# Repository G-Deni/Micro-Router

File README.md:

# Micro-Router
This project sets out to solve a simple but niche problem, when using any form of hot-spot in a large area coverage can suffer. Using a mesh-network of Micro-Routers coverage area can be extended for a short time without running any cables. This is achieved by a custom OpenWRT configuration and a onboard battery that should yield ~16hrs of run time.

## Features 

### SOM
Each Micro-Router uses a [Carambola2](https://www.8devices.com/products/carambola-2) SOM running [OpenWRT](https://openwrt.org/). 

### Ports
<ul>
  <li>USB-A - Media share capacity</li>
  <li>USB-C - Charging and UART</li>
  <li>2x RJ45 - LAN and WAN</li>
</ul>

### Charge Controller
Powered A 3.3v TP4056 charging circuit with a separate 5v boost converter to power the USB-A port. The charge controller was selected for this project to be cheap, this means while the battery is protected there is no communication between the SOM and the charge controller. There is no safe start of shut down if the battery dies the charge controller will disconnect the battery from the loads. It power switch toggles the boost converters on and off, disconnecting the battery from all loads at the boost converter. The 5v and the 3.3v boost converters are both 500mah and toggled on and off by the same slide switch.

### USB Serial
It has serial output over USB-C to help prevent bricking during development. All of the reset and clock pins are connected to make it as robust as possible, however if there is a problem with the serial connection both the Carambola2 and the serial to USB IC have reset push-buttons. 

### GPIO/SPI Headers
Exposed on the board are two 2.25mm pitch headers one is for SPI screen output (four pin) and one for general GPIO (6 pin).  

### External Antenna
A board mounted SMA connector is impedance matched for 2.4ghz WiFi is exposed for a external antenna to be connected to. There is no internal antenna as the performance is usually very poor.

### Speaker
Two pins are exposed for the speaker one is ground the other is a GPIO. One of the GPIO pins has to be reserved to be used as a speaker. If the extra GPIO pin is needed do not populate the speaker.

## Docking Case
The PCB layout may look rather unconventional but it is intentional. The routers are optimized to be used in a dock configuration.

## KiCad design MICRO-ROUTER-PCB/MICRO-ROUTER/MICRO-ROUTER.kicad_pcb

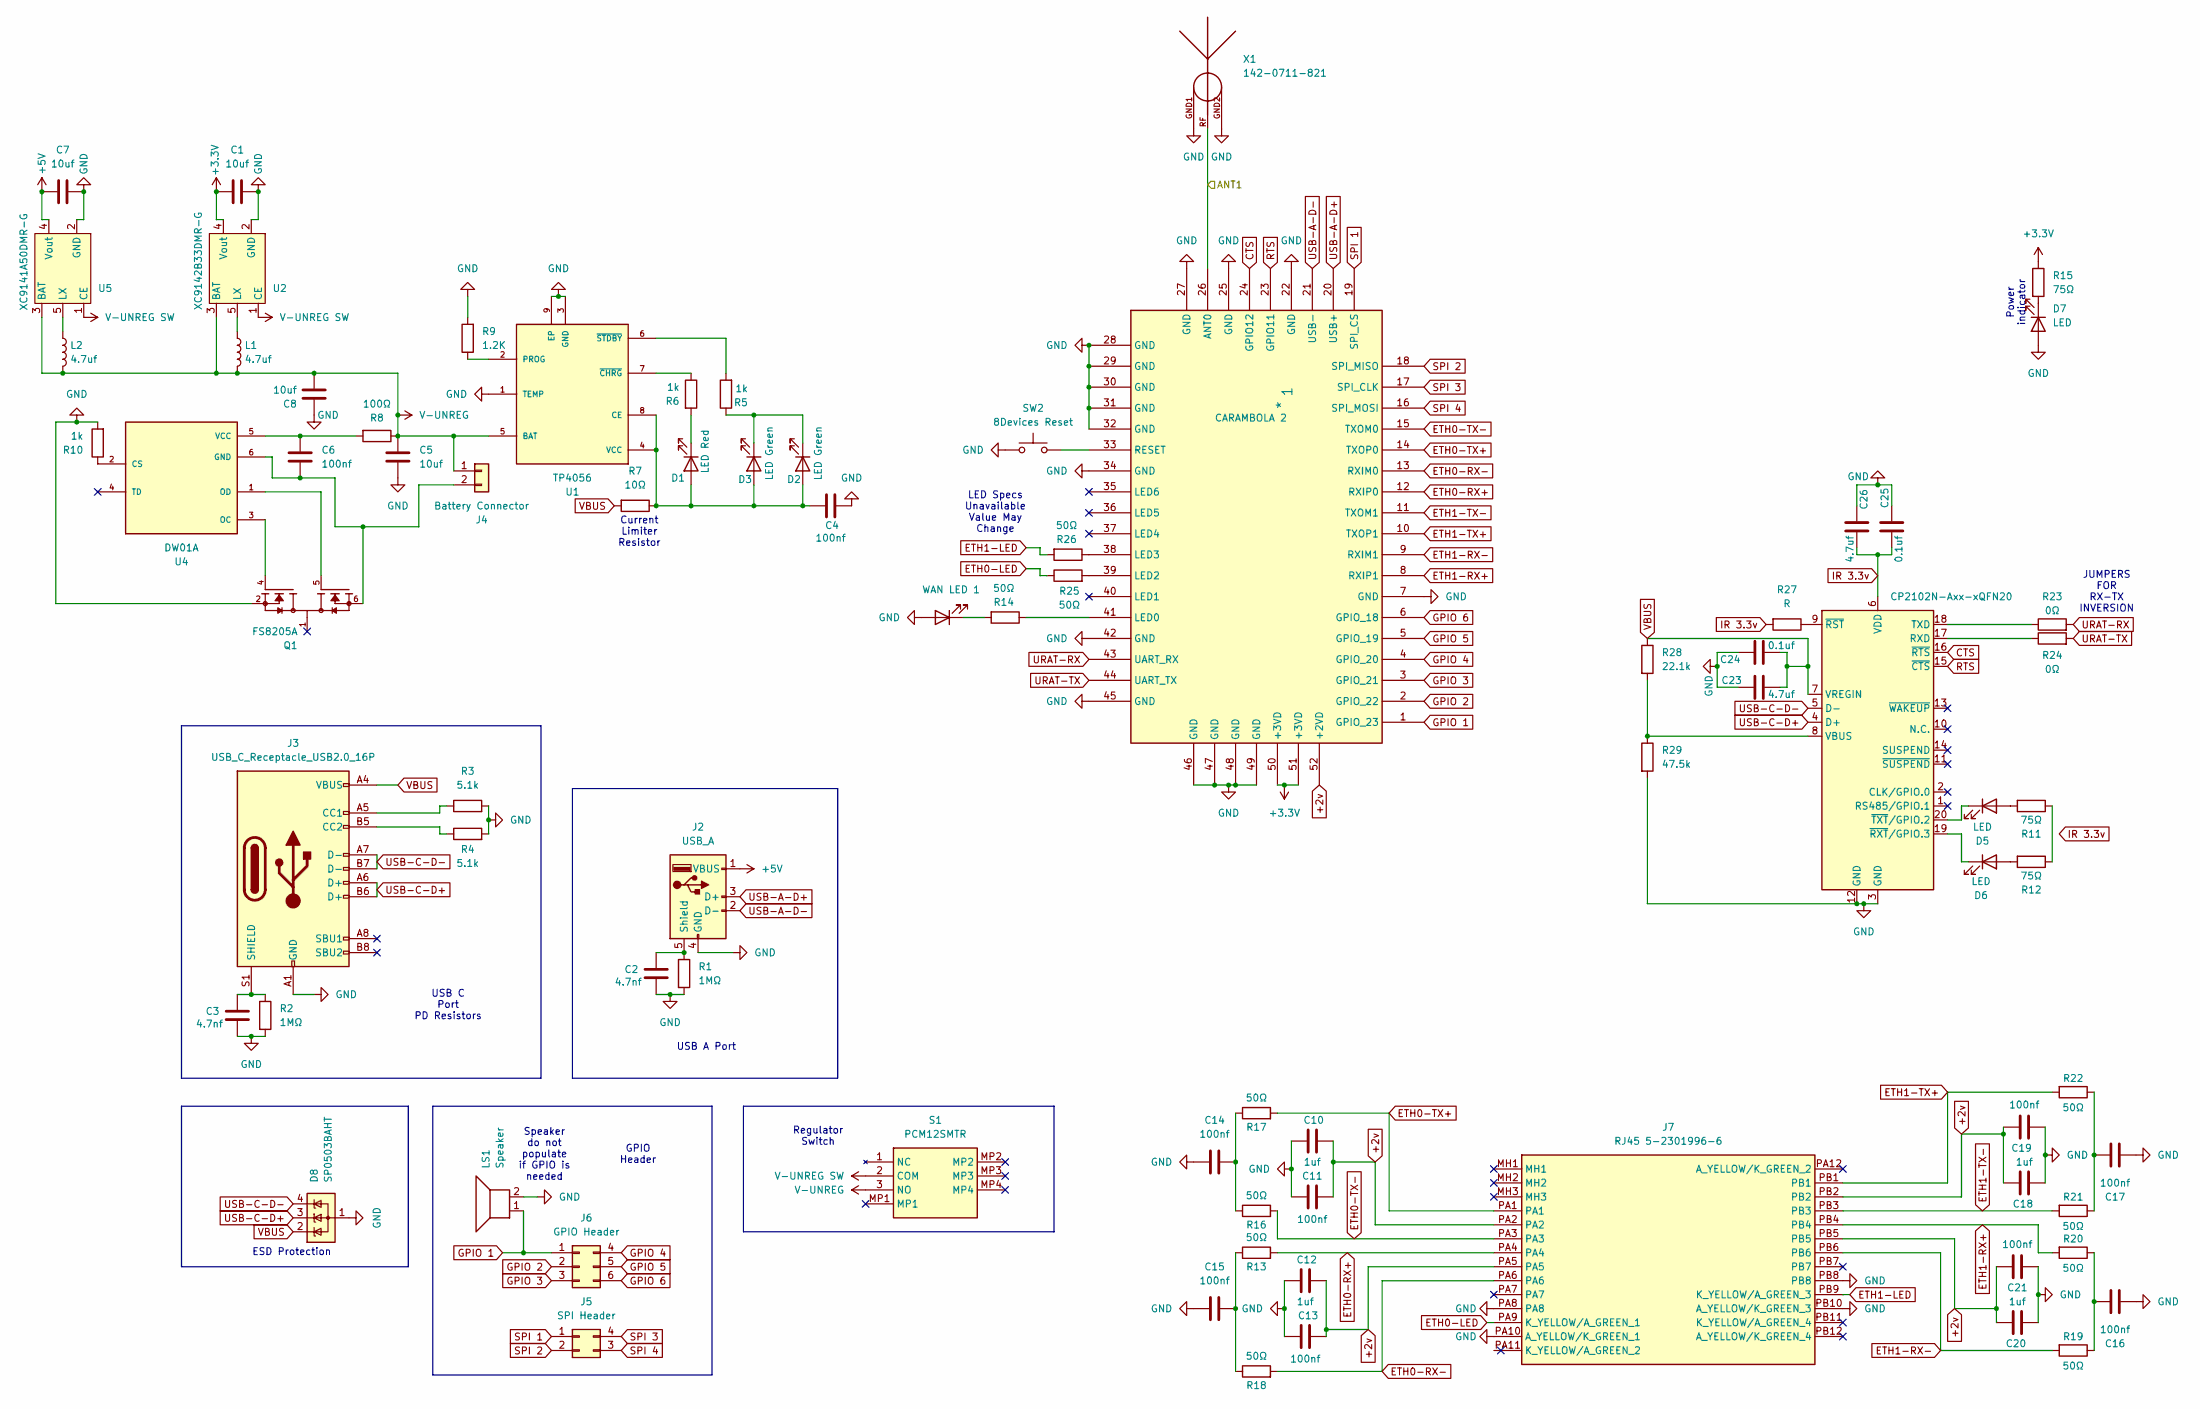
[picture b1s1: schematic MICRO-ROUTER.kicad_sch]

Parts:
1: *; 8Devices-Carambola2
C1, C5, C7, C8: 10uf; C_0603_1608Metric
C2, C3: 4.7nf; C_0603_1608Metric
C4, C6, C11, C13, C14, C15, C16, C17, C19, C21: 100nf; C_0603_1608Metric
C10, C12, C18, C20: 1uf; C_0603_1608Metric
C23, C26: 4.7uf
C24, C25: 0.1uf
D1: LED Red; LED_0603_1608Metric
D2, D3: LED Green; LED_0603_1608Metric
D4: WAN LED 1; LED_0603_1608Metric
D5, D6, D7: LED; LED_0603_1608Metric
D8: SP0503BAHT; SOT-143
J2: USB_A; USB_A_Molex_67643_Horizontal
J3: USB_C_Receptacle_USB2.0_16P; TYPE-C-31-M-12
J4: Battery Connector; PinSocket_1x02_P2.54mm_Vertical
J5: SPI Header; PinSocket_2x02_P2.54mm_Vertical
J6: GPIO Header; PinSocket_2x03_P2.54mm_Vertical
J7: RJ45 5-2301996-6; RJ45 523019966; Manufacturer_Part_Number 5-2301996-6; Mouser Part Number 571-5-2301996-6
L1, L2: 4.7uf; INDPM5752X300N
LS1: Speaker; PinSocket_1x02_P1.00mm_Vertical
Q1: FS8205A; PARTREV 1.7
R1, R2: 1MΩ; R_0603_1608Metric
R3, R4: 5.1k; R_0603_1608Metric
R5, R6, R10: 1k; R_0603_1608Metric
R7: 10Ω; R_0603_1608Metric
R8: 100Ω; R_0603_1608Metric
R9: 1.2K; R_0603_1608Metric
R11, R12, R15: 75Ω; R_0603_1608Metric
R13, R14, R16, R17, R18, R19, R20, R21, R22, R25, R26: 50Ω; R_0603_1608Metric
R23, R24: 0Ω; R_0603_1608Metric
R27: R
R28: 22.1k
R29: 47.5k
S1: PCM12SMTR; Manufacturer_Part_Number PCM12SMTR; Mouser Part Number 611-PCM12SMTR
SW2: 8Devices Reset; SW_PUSH_6mm
U1: TP4056
U2: XC9142B33DMR-G; XC8107AC20MR-G
U3: CP2102N-Axx-xQFN20; SiliconLabs_QFN-20-1EP_3x3mm_P0.5mm_EP1.8x1.8mm
U4: DW01A; PARTREV 1.8
U5: XC9141A50DMR-G; XC8107AC20MR-G
X1: 142-0711-821; SMA 142-0711-821

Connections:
+2v: 1.52 (+2VD), C10.2, C11.2, C12.2, C13.2, C18.2, C19.2, C20.2, C21.2, J7.PA2, J7.PA5, J7.PB2, J7.PB5
+3.3V: 1.50 (+3VD), 1.51 (+3VD), C1.1, R15.1, U2.4 (Vout)
+5V: C7.1, J2.1 (VBUS), U5.4 (Vout)
/ANT1: 1.26 (ANT0), X1.RF
CTS: 1.24 (GPIO12), U3.16 (~RTS)
ETH0-LED: J7.PA9 (K_YELLOW/A_GREEN_1), R25.1
ETH0-RX+: 1.12 (RXIP0), J7.PA4, R13.2
ETH0-RX-: 1.13 (RXIM0), J7.PA6, R18.2
ETH0-TX+: 1.14 (TXOP0), J7.PA1, R17.2
ETH0-TX-: 1.15 (TXOM0), J7.PA3, R16.2
ETH1-LED: J7.PB9 (K_YELLOW/A_GREEN_3), R26.2
ETH1-RX+: 1.8 (RXIP1), J7.PB4, R20.2
ETH1-RX-: 1.9 (RXIM1), J7.PB6, R19.2
ETH1-TX+: 1.10 (TXOP1), J7.PB1, R22.2
ETH1-TX-: 1.11 (TXOM1), J7.PB3, R21.2
GND: 1.7 (GND), 1.22 (GND), 1.25 (GND), 1.27 (GND), 1.28 (GND), 1.29 (GND), 1.30 (GND), 1.31 (GND), 1.32 (GND), 1.34 (GND), 1.42 (GND), 1.45 (GND), 1.46 (GND), 1.47 (GND), 1.48 (GND), 1.49 (GND), C1.2, C2.2, C3.2, C4.1, C5.1, C7.2, C8.2, C10.1, C11.1, C12.1, C13.1, C14.1, C15.1, C16.1, C17.1, C18.1, C19.1, C20.1, C21.1, C23.2, C24.2, C25.2, C26.2, D4.2 (A), D7.2 (A), D8.1 (A), J2.4 (GND), J3.A1 (GND), J3.A12 (GND), J3.B1 (GND), J3.B12 (GND), J7.PA8, J7.PA10 (A_YELLOW/K_GREEN_1), J7.PB8, J7.PB10 (A_YELLOW/K_GREEN_3), LS1.2, Q1.2, Q1.3, R1.2, R2.2, R3.2, R4.2, R9.2, R10.2, R29.2, SW2.1, U1.1 (TEMP), U1.3 (GND), U1.9 (EP), U2.2 (GND), U3.3 (GND), U3.12 (GND), U3.21 (GND), U5.2 (GND), X1.GND1, X1.GND2
GPIO 1: 1.1 (GPIO_23), J6.1, LS1.1
GPIO 2: 1.2 (GPIO_22), J6.2
GPIO 3: 1.3 (GPIO_21), J6.3
GPIO 4: 1.4 (GPIO_20), J6.4
GPIO 5: 1.5 (GPIO_19), J6.5
GPIO 6: 1.6 (GPIO_18), J6.6
unnamed: 1.41 (LED0), R14.1
unnamed: 1.39 (LED2), R25.2
unnamed: 1.38 (LED3), R26.1
unnamed: 1.33 (RESET), SW2.2
unnamed: C14.2, R16.1, R17.1
unnamed: C15.2, R13.1, R18.1
unnamed: C16.2, R19.1, R20.1
unnamed: C17.2, R21.1, R22.1
unnamed: C4.2, D1.2 (A), D2.2 (A), D3.2 (A), R7.1, U1.4 (VCC), U1.8 (CE)
unnamed: D1.1 (K), R6.2
unnamed: D2.1 (K), D3.1 (K), R5.1
unnamed: D4.1 (K), R14.2
unnamed: D5.2 (A), R11.2
unnamed: D5.1 (K), U3.20 (~TXT/GPIO.2)
unnamed: D6.2 (A), R12.2
unnamed: D6.1 (K), U3.19 (~RXT/GPIO.3)
unnamed: D7.1 (K), R15.2
unnamed: C2.1, J2.5 (Shield), R1.1
unnamed: J3.A5 (CC1), R3.1
unnamed: J3.B5 (CC2), R4.1
unnamed: C3.1, J3.S1 (SHIELD), R2.1
unnamed: C6.1, J4.2, Q1.6, Q1.7, U4.6 (GND)
unnamed: R9.1, U1.2 (PROG)
unnamed: R6.1, U1.7 (~CHRG)
unnamed: R5.2, U1.6 (~STDBY)
unnamed: L1.1, U2.5 (LX)
unnamed: R24.1, U3.17 (RXD)
unnamed: R23.1, U3.18 (TXD)
unnamed: R28.2, R29.1, U3.8 (VBUS)
unnamed: R27.1, U3.9 (~RST)
unnamed: R10.1, U4.2 (CS)
unnamed: Q1.4, U4.3 (OC)
unnamed: Q1.5, U4.1 (OD)
unnamed: C6.2, R8.2, U4.5 (VCC)
unnamed: L2.1, U5.5 (LX)
RTS: 1.23 (GPIO11), U3.15 (~CTS)
SPI 1: 1.19 (SPI_CS), J5.1
SPI 2: 1.18 (SPI_MISO), J5.2
SPI 3: 1.17 (SPI_CLK), J5.4
SPI 4: 1.16 (SPI_MOSI), J5.3
URAT-RX: 1.43 (UART_RX), R23.2
URAT-TX: 1.44 (UART_TX), R24.2
USB-A-D+: 1.20 (USB+), J2.3 (D+)
USB-A-D-: 1.21 (USB-), J2.2 (D-)
USB-C-D+: D8.3 (K), J3.A6 (D+), J3.B6 (D+), U3.4 (D+)
USB-C-D-: D8.4 (K), J3.A7 (D-), J3.B7 (D-), U3.5 (D-)
V-UNREG: C5.2, C8.1, J4.1, L1.2, L2.2, R8.1, S1.3 (NO), U1.5 (BAT), U2.3 (BAT), U5.3 (BAT)
V-UNREG SW: S1.2 (COM), U2.1 (CE), U5.1 (CE)
VBUS: C23.1, C24.1, D8.2 (K), J3.A4 (VBUS), J3.A9 (VBUS), J3.B4 (VBUS), J3.B9 (VBUS), R7.2, R28.1, U3.7 (VREGIN)

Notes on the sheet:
JUMPERS FOR RX-TX INVERSION
ESD Protection
Current Limiter Resistor
USB A Port
Power indicator
Speaker do not populate if GPIO is needed
Regulator Switch
USB C Port PD Resistors
GPIO Header
LED Specs Unavailable Value May Change

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
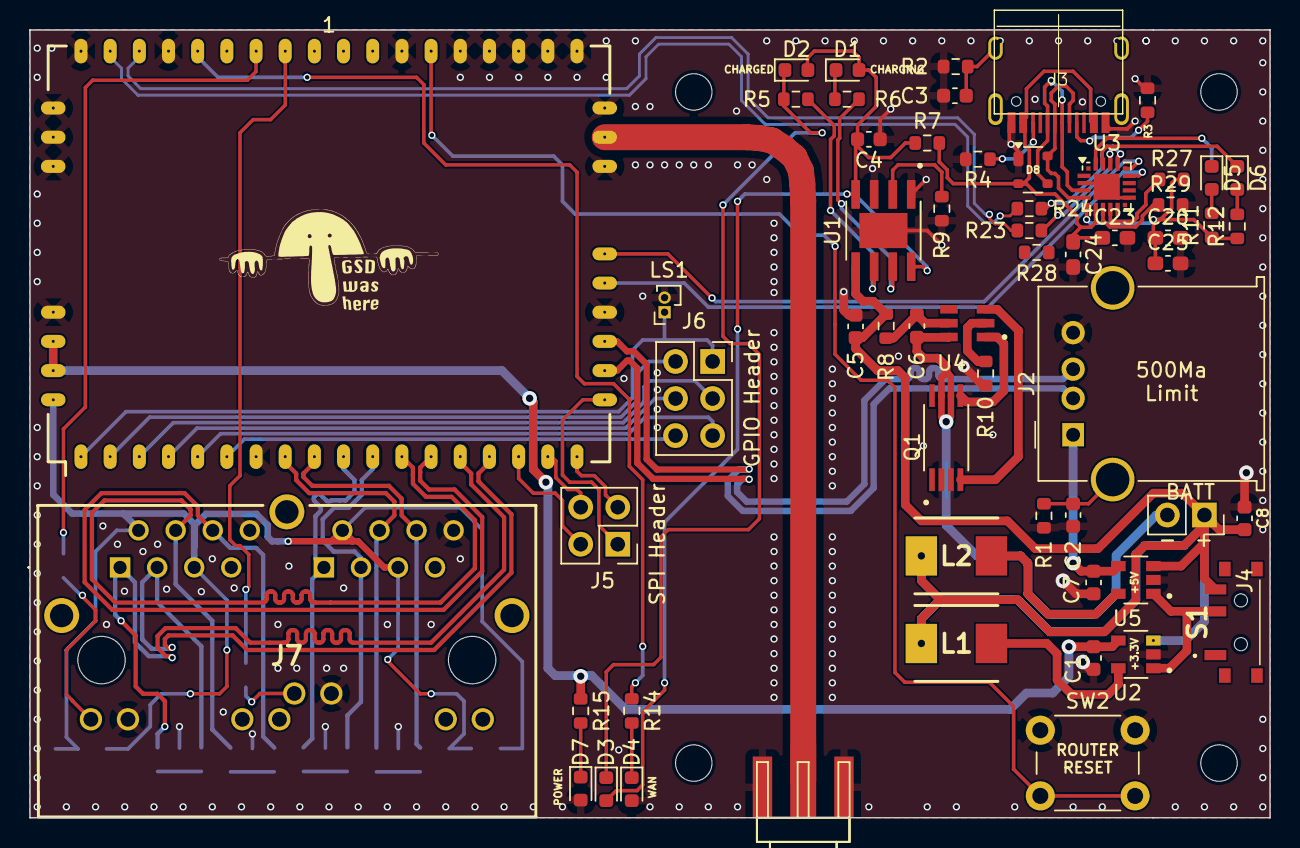
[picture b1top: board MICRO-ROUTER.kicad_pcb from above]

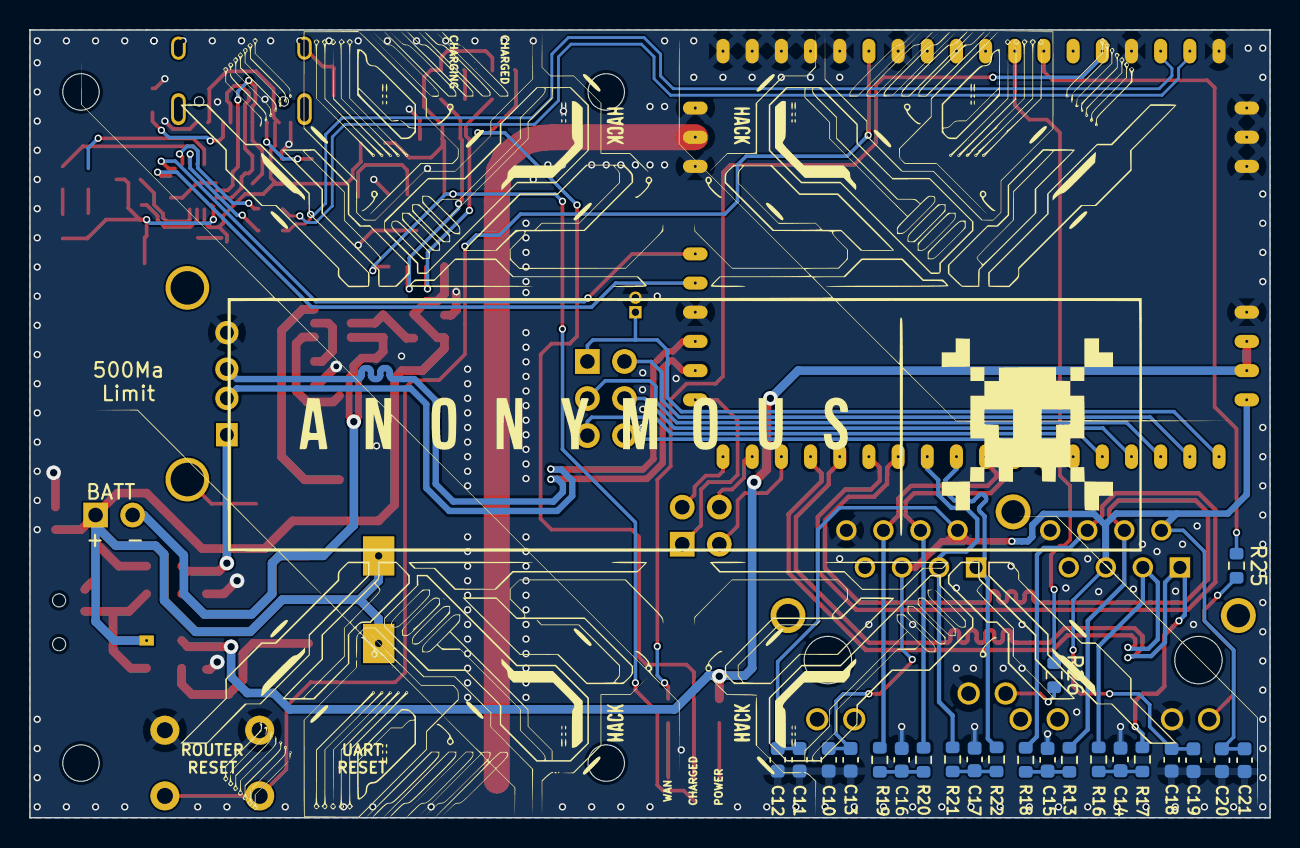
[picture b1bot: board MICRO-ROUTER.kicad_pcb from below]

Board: 2 copper layers, 85.0 x 54.0 mm, 80 parts (22 on the bottom side), 72 nets.

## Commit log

2024-04-26 Update README.md
    quick wright up
2024-04-29 Intal commit after https vs ssh fix
2024-05-01 Started work on schem, finished voltage reg and charge daughter board
2024-05-02 Added USB 3.0 Started adding onboard URAT to TTL
2024-05-05 routine back up
2024-05-08 Swapped SOM due to lower wattage Worked on scematic -UART IC -USB C PORT -USB 2.0 PORT
2024-05-12 finished charger
2024-05-13 Added V regulator Added GPIO header Added SPI header Added WAN LED Fixed incorect component values Added tags for LAN
2024-05-14 Fixed rx tx LEDs Did footprint asociation
2024-05-14 Update README.md
    Updated to reflect hardware changes
2024-05-21 wirred rj45 port and power
2024-05-28 -Finish rj45 leds -Added notes to schem -Fixed missing footprints -Preped for layout -Wired Eth1
2024-05-28 fixed footprint error
2024-05-29 -began layout -fixed several errors in formating -fixed assocition errors
2024-05-30 -worked on more layout
2024-05-30 - Finished Usb C layout
2024-06-04 routed rj45 lines
2024-06-04 -wired sma connector
2024-06-07 -added extra charge LED -wired TP4056
2024-06-09 -Wired up Mofset
2024-06-20 fixed reg
2024-06-21 -wired 5v and 3.3v reg -cleaned up remaining footprints
2024-06-23 wired power rails
2024-06-24 wired cap array for rj45
2024-06-25 finished layout
2024-06-25 Update README.md
    Better description
2024-06-25 -Finished layout -Added GND vias -Added rendering photo -3d model association
2024-07-08 - fixed skew - fixed GND islands - moved some dif pairs to reduce loss - added silk
2024-07-08 -added decrotive silk -ran drc -fixed small layout errors
2024-07-13 -added output files for rev00
2024-07-24 Update README.md
    Updated readme
2024-07-24 Update README.md
    added pic
2024-07-24 adeed bom
2024-09-01 -fixed all open issues in the schematic
2024-09-01 spell checked readme
2024-09-08 -Unrouted PCB Errors
2024-12-22 -Fixed the ttl adapter (this time should be right)
2025-02-14 backup before wipe
